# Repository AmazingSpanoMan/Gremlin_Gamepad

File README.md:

# Gremlin Gamepad

Custom ergonomic analog gaming keypad powered by **ZMK Firmware**, **Nice!Nano v2** (nRF52840), **Nice!View** (Sharp Memory LCD 160×68), and a **Nintendo Switch Joy-Con analog thumbstick**.

---

## Repository Structure

```text
Gremlin_Gamepad/
├── .github/workflows/          # Automated ZMK cloud firmware build via GitHub Actions
├── boards/shields/gremlinv3/   # Gremlin v3 hardware shield definition
│   ├── src/                    # Custom LVGL status screen & 64x64 Gremlin mascot animations
│   ├── gremlinv3.overlay       # Devicetree pin assignments, matrix, ADC, and SPI display
│   ├── gremlinv3.conf          # Default shield Kconfig options
│   └── gremlinv3.keymap        # Default matrix layout and bindings
├── config/                     # User configuration & keymap
│   ├── gremlinv3.conf          # Active ZMK features (ZMK Studio, Display, SAADC, BLE)
│   ├── gremlinv3.keymap        # User-customizable keymap with ZMK Studio support
│   └── west.yml                # Manifest pinning ZMK v0.3 & Joy-Con analog stick driver
├── zephyr/                     # Module configuration for CMake and Zephyr build system
├── build.yaml                  # ZMK automated build matrix definition
├── CMakeLists.txt              # CMake build targets for custom display widgets and art
│
├── Gremlin_v3/                 # Gremlin v3 Hardware Engineering Files
│   ├── KiCad/                  # Schematic, PCB layout, JLCPCB Gerbers, CPL (Pick & Place), BOM
│   ├── CAD_Files/              # 3D enclosure models, ScottoCaps keycaps, and STEP assemblies
│   └── CNC_Files/              # Carvera CNC isolation milling NC files and tooling
│
├── Gremlin_v2/                 # Legacy Gremlin v2 design files & firmware archive
└── Gremlin_v1/                 # Legacy Gremlin v1 firmware archive
```

---

## Firmware Features

* **ZMK Studio Ready:** Live key remapping on the fly without reflashing.
* **Analog Thumbstick:** Direct SAADC sampling of Nintendo Switch Joy-Con analog stick with 8-way digital emulation or mouse emulation. Complete setup and tuning instructions: [**Joystick Calibration & Driver Guide**](JOYSTICK_CALIBRATION_GUIDE.md).
* **Custom Nice!View Display:**
  * **Boot Screen:** Animated Gremlin startup logo.
  * **Active Screen:** 64×64 animated Gremlin mascot (Prowl, Twitch, Snarl, Claw Slash) alongside real-time Battery %, BLE profile, and active Layer name.
  * **Standby Screen:** Curled-up gargoyle sleeping mode with low-power screen idle to maximize battery life.

---

## Hardware Production Files

All hardware manufacturing files are located in [`Gremlin_v3/`](Gremlin_v3/):
* **PCB Fabrication & SMT Assembly:** [`Gremlin_v3/KiCad/Gremlin_v3/`](Gremlin_v3/KiCad/Gremlin_v3/)
  * Ready-to-order Gerbers: `Gremlin_v3_JLCPCB.zip`
  * Complete PCBA Assembly Package (Gerbers + CPL + BOM): `Gremlin_v3_JLCPCB_Assembly_Package.zip`
* **3D Printing & CAD:** [`Gremlin_v3/CAD_Files/`](Gremlin_v3/CAD_Files/)
* **CNC Milling:** [`Gremlin_v3/CNC_Files/`](Gremlin_v3/CNC_Files/)

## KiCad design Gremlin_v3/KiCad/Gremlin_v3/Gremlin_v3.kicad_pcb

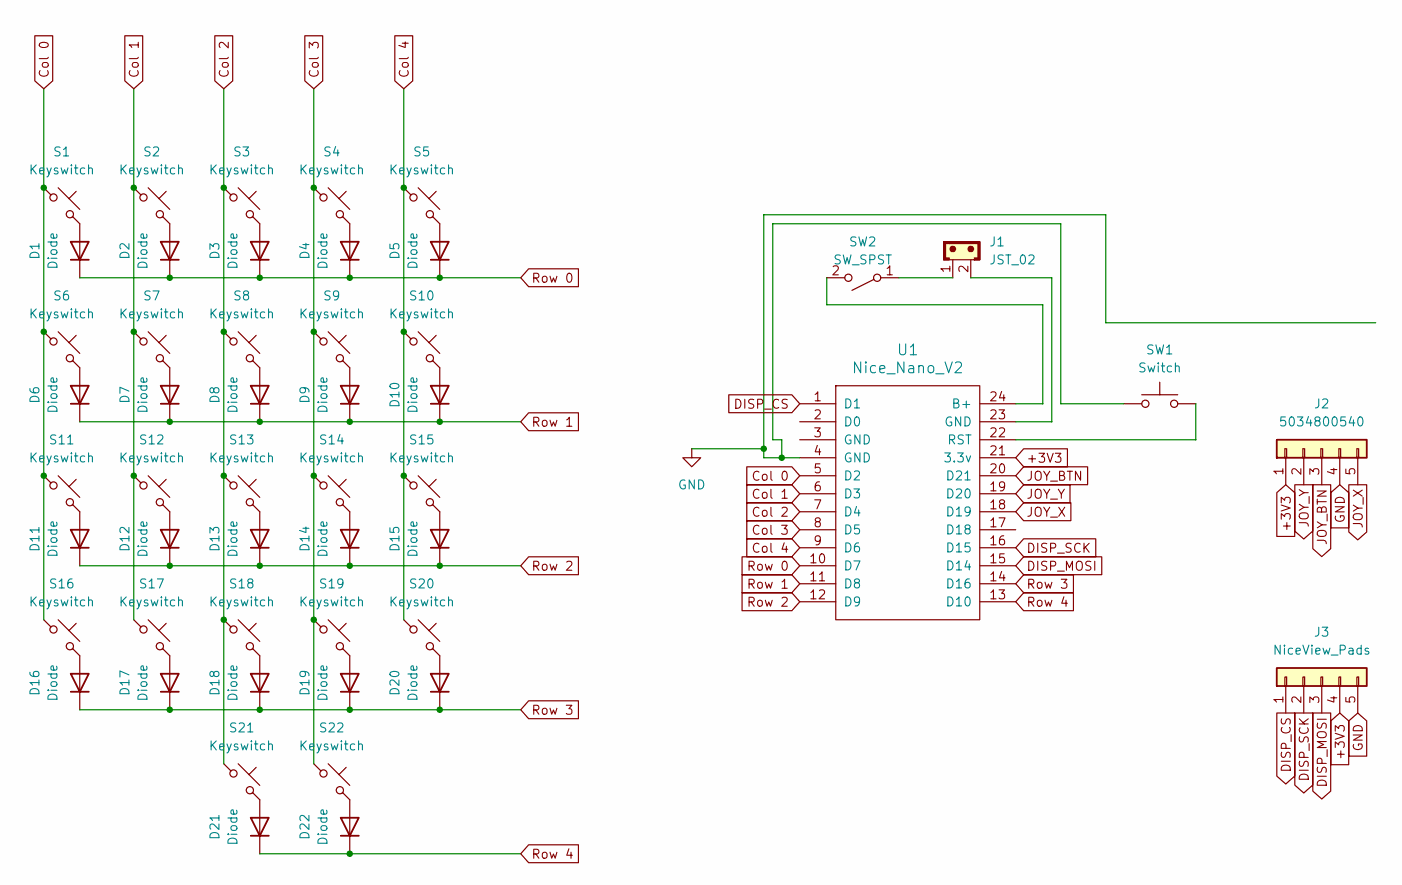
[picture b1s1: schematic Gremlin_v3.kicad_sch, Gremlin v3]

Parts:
D1, D2, D3, D4, D5, D6, D7, D8, D9, D10, D11, D12, D13, D14, D15, D16, D17, D18, D19, D20, D21, D22: Diode; Diode_SOD-123
J1: JST_02; JST_EH_S2B-EH_1x02_P2.50mm_Horizontal
J2: 5034800540; CONN_503480-0540_MOL
J3: NiceView_Pads; PinHeader_1x05_P2.54mm_Vertical
S1, S2, S3, S4, S5, S6, S7, S8, S9, S10, S11, S12, S13, S14, S15, S16, S17, S18, S19, S20, S21, S22: Keyswitch; Hotswap_Choc_V1
SW1: Switch; Panasonic_EVQPUJ_EVQPUA
SW2: SW_SPST; SW_SPDT_PCM12
U1: Nice_Nano_V2

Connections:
+3V3: J2.1, J3.4, U1.21 (3.3v)
Col 0: S1.1, S6.1, S11.1, S16.1, U1.5 (D2)
Col 1: S2.1, S7.1, S12.1, S17.1, U1.6 (D3)
Col 2: S3.1, S8.1, S13.1, S18.1, S21.1, U1.7 (D4)
Col 3: S4.1, S9.1, S14.1, S19.1, S22.1, U1.8 (D5)
Col 4: S5.1, S10.1, S15.1, S20.1, U1.9 (D6)
DISP_CS: J3.1, U1.1 (D1)
DISP_MOSI: J3.3, U1.15 (D14)
DISP_SCK: J3.2, U1.16 (D15)
GND: J2.4, J3.5, SW1.1, U1.4 (GND)
JOY_BTN: J2.3, U1.20 (D21)
JOY_X: J2.5, U1.18 (D19)
JOY_Y: J2.2, U1.19 (D20)
unnamed: D1.2 (A), S1.2
unnamed: D2.2 (A), S2.2
unnamed: D3.2 (A), S3.2
unnamed: D4.2 (A), S4.2
unnamed: D5.2 (A), S5.2
unnamed: D6.2 (A), S6.2
unnamed: D7.2 (A), S7.2
unnamed: D8.2 (A), S8.2
unnamed: D9.2 (A), S9.2
unnamed: D10.2 (A), S10.2
unnamed: D11.2 (A), S11.2
unnamed: D12.2 (A), S12.2
unnamed: D13.2 (A), S13.2
unnamed: D14.2 (A), S14.2
unnamed: D15.2 (A), S15.2
unnamed: D16.2 (A), S16.2
unnamed: D17.2 (A), S17.2
unnamed: D18.2 (A), S18.2
unnamed: D19.2 (A), S19.2
unnamed: D20.2 (A), S20.2
unnamed: D21.2 (A), S21.2
unnamed: D22.2 (A), S22.2
unnamed: J1.2, U1.23 (GND)
unnamed: J1.1, SW2.1 (A)
unnamed: SW2.2 (B), U1.24 (B+)
unnamed: SW1.2, U1.22 (RST)
Row 0: D1.1 (K), D2.1 (K), D3.1 (K), D4.1 (K), D5.1 (K), U1.10 (D7)
Row 1: D6.1 (K), D7.1 (K), D8.1 (K), D9.1 (K), D10.1 (K), U1.11 (D8)
Row 2: D11.1 (K), D12.1 (K), D13.1 (K), D14.1 (K), D15.1 (K), U1.12 (D9)
Row 3: D16.1 (K), D17.1 (K), D18.1 (K), D19.1 (K), D20.1 (K), U1.14 (D16)
Row 4: D21.1 (K), D22.1 (K), U1.13 (D10)

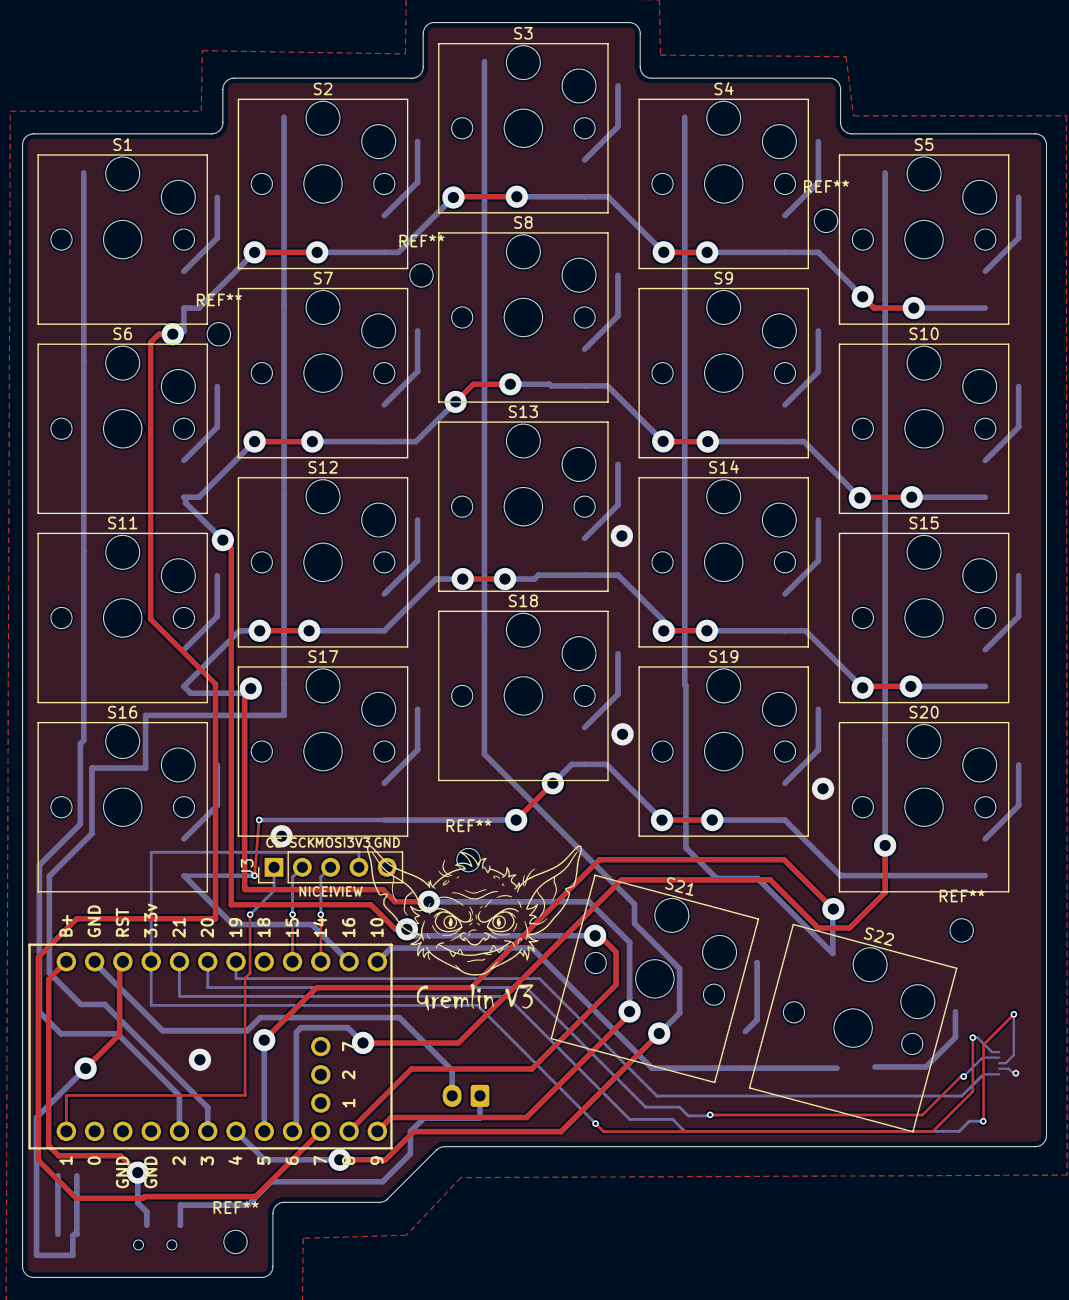
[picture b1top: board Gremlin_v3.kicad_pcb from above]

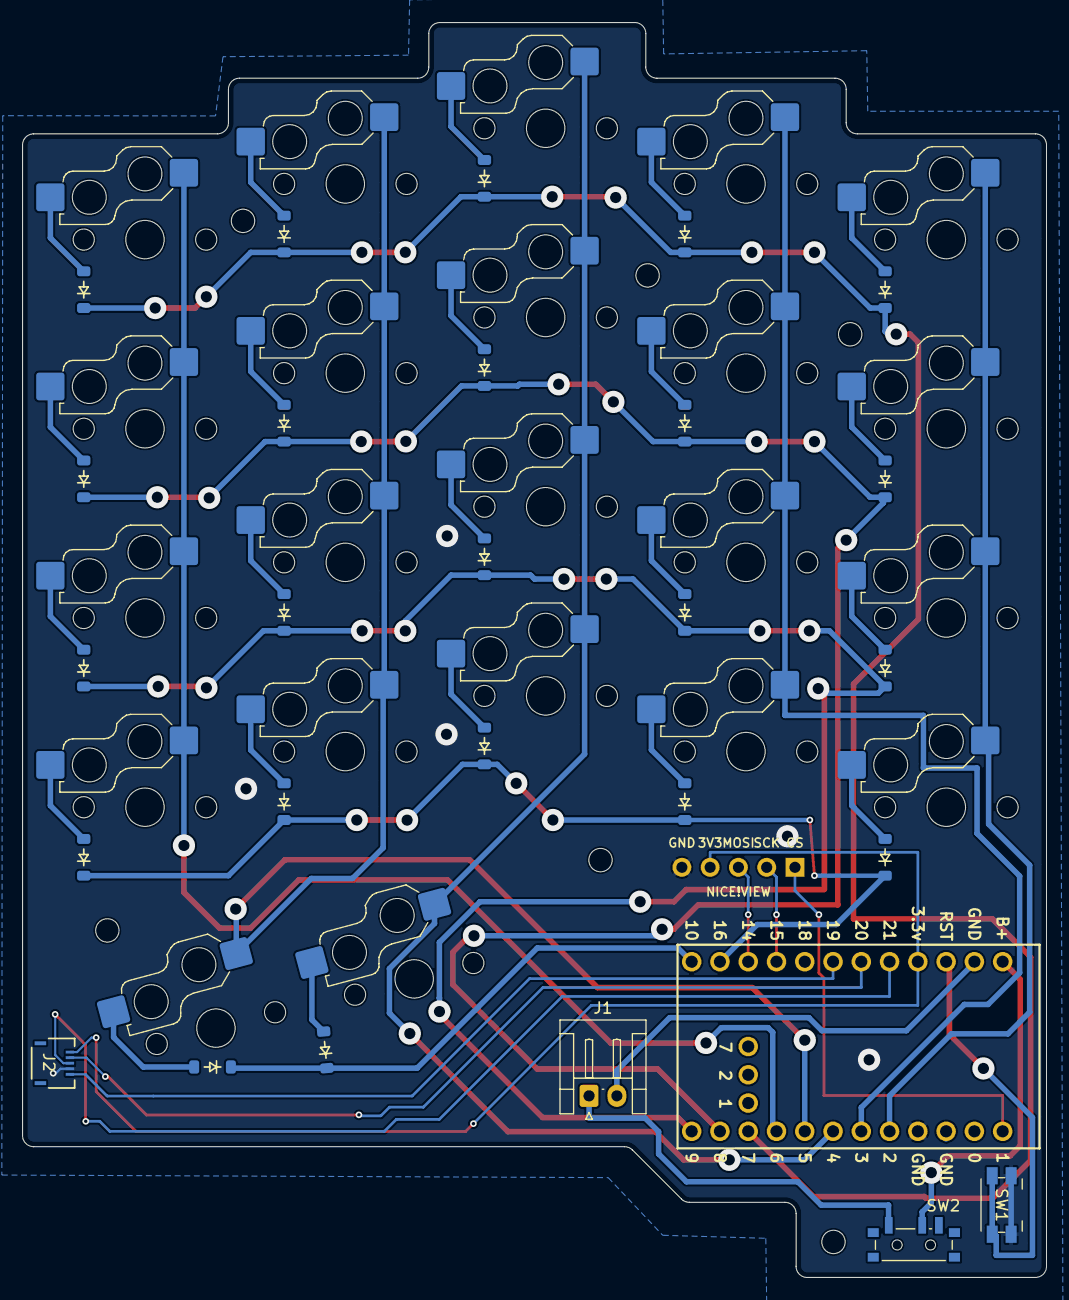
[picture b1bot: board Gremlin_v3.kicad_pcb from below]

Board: 2 copper layers, 92.0 x 112.8 mm, 50 parts (26 on the bottom side), 44 nets.

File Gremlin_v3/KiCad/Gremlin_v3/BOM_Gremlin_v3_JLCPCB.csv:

Comment,Designator,Footprint,LCSC Part #,Type,Layer
1N4148W (Switch Matrix Isolation Diodes),"D1,D2,D3,D4,D5,D6,D7,D8,D9,D10,D11,D12,D13,D14,D15,D16,D17,D18,D19,D20,D21,D22",Diode_SOD-123,C81598,SMD,Bottom
503480-0540 (0.5mm Pitch 5-Pin FPC Joy-Con Connector),J2,CONN_503480-0540_MOL,C262325,SMD,Bottom
"Tactile Push Button (Reset Switch, 4.7x3.5mm)",SW1,Panasonic_EVQPUJ_EVQPUA,C318884,SMD,Bottom
"SPDT Slide Switch (Power On/Off, PCM12 / MSK-12D19)",SW2,SW_SPDT_PCM12,C37694,SMD,Bottom
Kailh Choc V1 Hotswap Sockets (PG1350),"S1,S2,S3,S4,S5,S6,S7,S8,S9,S10,S11,S12,S13,S14,S15,S16,S17,S18,S19,S20,S21,S22",Hotswap_Choc_V1,C2895697,SMD,Top
JST-EH 2-Pin 2.50mm Horizontal Battery Header,J1,JST_EH_S2B-EH_1x02_P2.50mm_Horizontal,C295744,THT,Bottom
Nice!Nano v2 Controller Pin Headers (2x 12-pin 2.54mm),U1,Nice_Nano_V2,Hand-Solder / Socketed,THT,Top

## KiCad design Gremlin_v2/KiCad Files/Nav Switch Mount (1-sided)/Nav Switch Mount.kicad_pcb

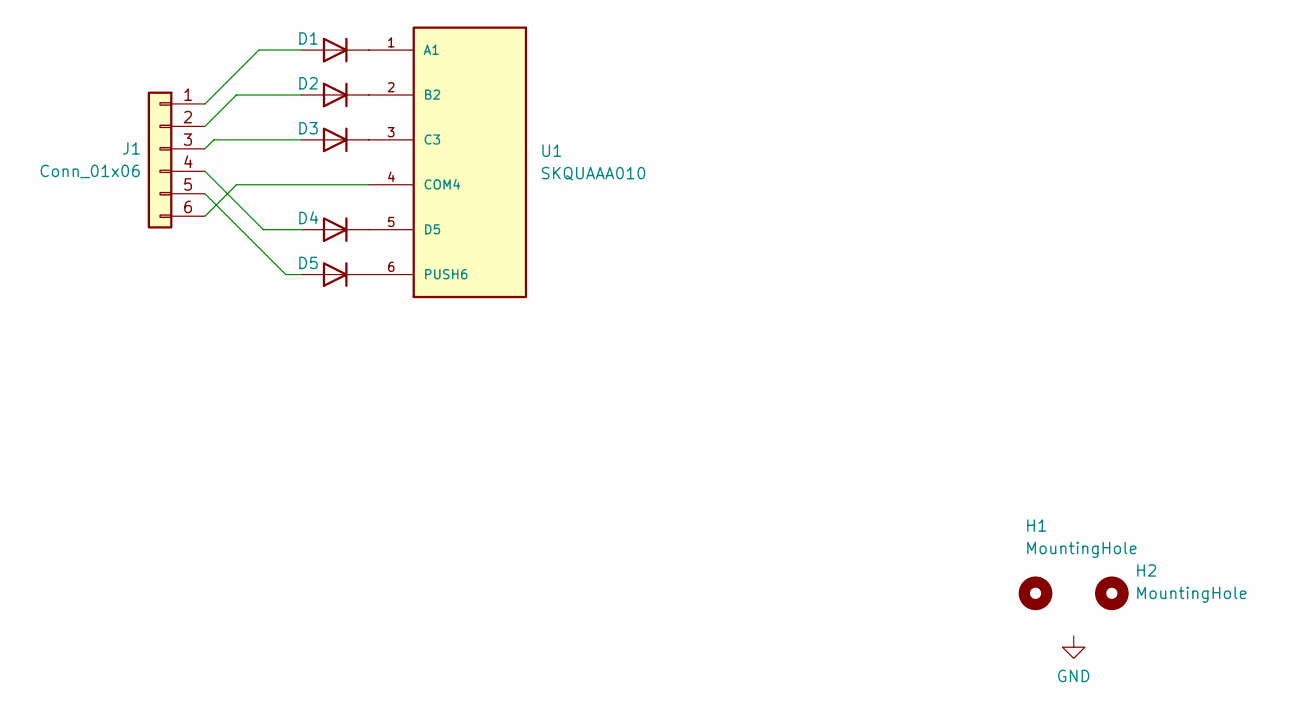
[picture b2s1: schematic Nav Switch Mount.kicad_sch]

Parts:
D1, D2, D3, D4, D5: D; D_SOD-123
H1, H2: MountingHole; MountingHole_2.1mm
J1: Conn_01x06; Header_2x3
U1: SKQUAAA010; Nav_Switch_SKQUAAA010

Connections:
unnamed: D1.2 (A), J1.1
unnamed: D1.1 (K), U1.1 (A1)
unnamed: D2.2 (A), J1.2
unnamed: D2.1 (K), U1.2 (B2)
unnamed: D3.2 (A), J1.3
unnamed: D3.1 (K), U1.3 (C3)
unnamed: D4.2 (A), J1.4
unnamed: D4.1 (K), U1.5 (D5)
unnamed: D5.2 (A), J1.5
unnamed: D5.1 (K), U1.6 (PUSH6)
unnamed: J1.6, U1.4 (COM4)

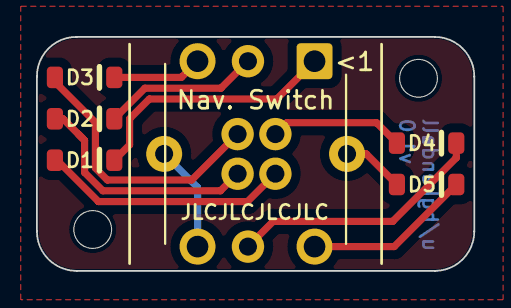
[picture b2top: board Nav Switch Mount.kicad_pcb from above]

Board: 2 copper layers, 24.3 x 13.0 mm, 9 parts (1 on the bottom side), 11 nets.

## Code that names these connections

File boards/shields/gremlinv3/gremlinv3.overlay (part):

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 * Nordic SAADC CH[n].PSELP register values:
 * In nRF52840 SAADC hardware and nrfx HAL (nrf_saadc.h):
 *   0 = NC (Not Connected / Input Disabled)
 *   1 = AIN0 (P0.02 / Header Pin 18 / Silk 19 -> J2 Pin 1 JOY_X)
 *   2 = AIN1 (P0.03)
 *   3 = AIN2 (P0.04)
 *   4 = AIN3 (P0.05)
 *   5 = AIN4 (P0.28)
 *   6 = AIN5 (P0.29 / Header Pin 19 / Silk 20 -> J2 Pin 4 JOY_Y)
 *   7 = AIN6 (P0.30)
 *   8 = AIN7 (P0.31 / Header Pin 20 / Silk 21 -> J2 Pin 3 JOY_BTN)
 * Zephyr's adc_nrfx_saadc.c assigns positive_inputs directly to PSELP.
 */
#undef NRF_SAADC_AIN0
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    };
};

/* Explicitly disable hardware UART0 to release P0.06 (Header Pin 1 / Silk 0) for DISP_CS */
&uart0 {
    status = "disabled";
};
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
